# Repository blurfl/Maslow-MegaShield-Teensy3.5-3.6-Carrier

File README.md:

# Maslow-MegaShield-Teensy3.5-3.6-Carrier
Carrier board to connect a Teensy 3.5 or 3.6 to a Maslow MegaShield motor control board
======================

***
Layout

***
Schematic

***
Notes

 Most of the pin assignments match the Arduino Mega. IN5 & IN6 were changed so that they would be PWM capable (for a different project). The AUX pins were re-arranged for convenience of layout. The board version detection was not implemented, as that would tie up four more gpio pins. 
 
 There is provision to choose the voltage used for the encoders, either the 5V from the USB connection or the 3V3 regulated by the Teensy. It is strapped for 3V3, and that seems to work well on the Teensy 3.5 I've tested. The Teensy 3.6 would be damaged by using more than 3V3 in its inputs.

 The JTAG parts are not tested.

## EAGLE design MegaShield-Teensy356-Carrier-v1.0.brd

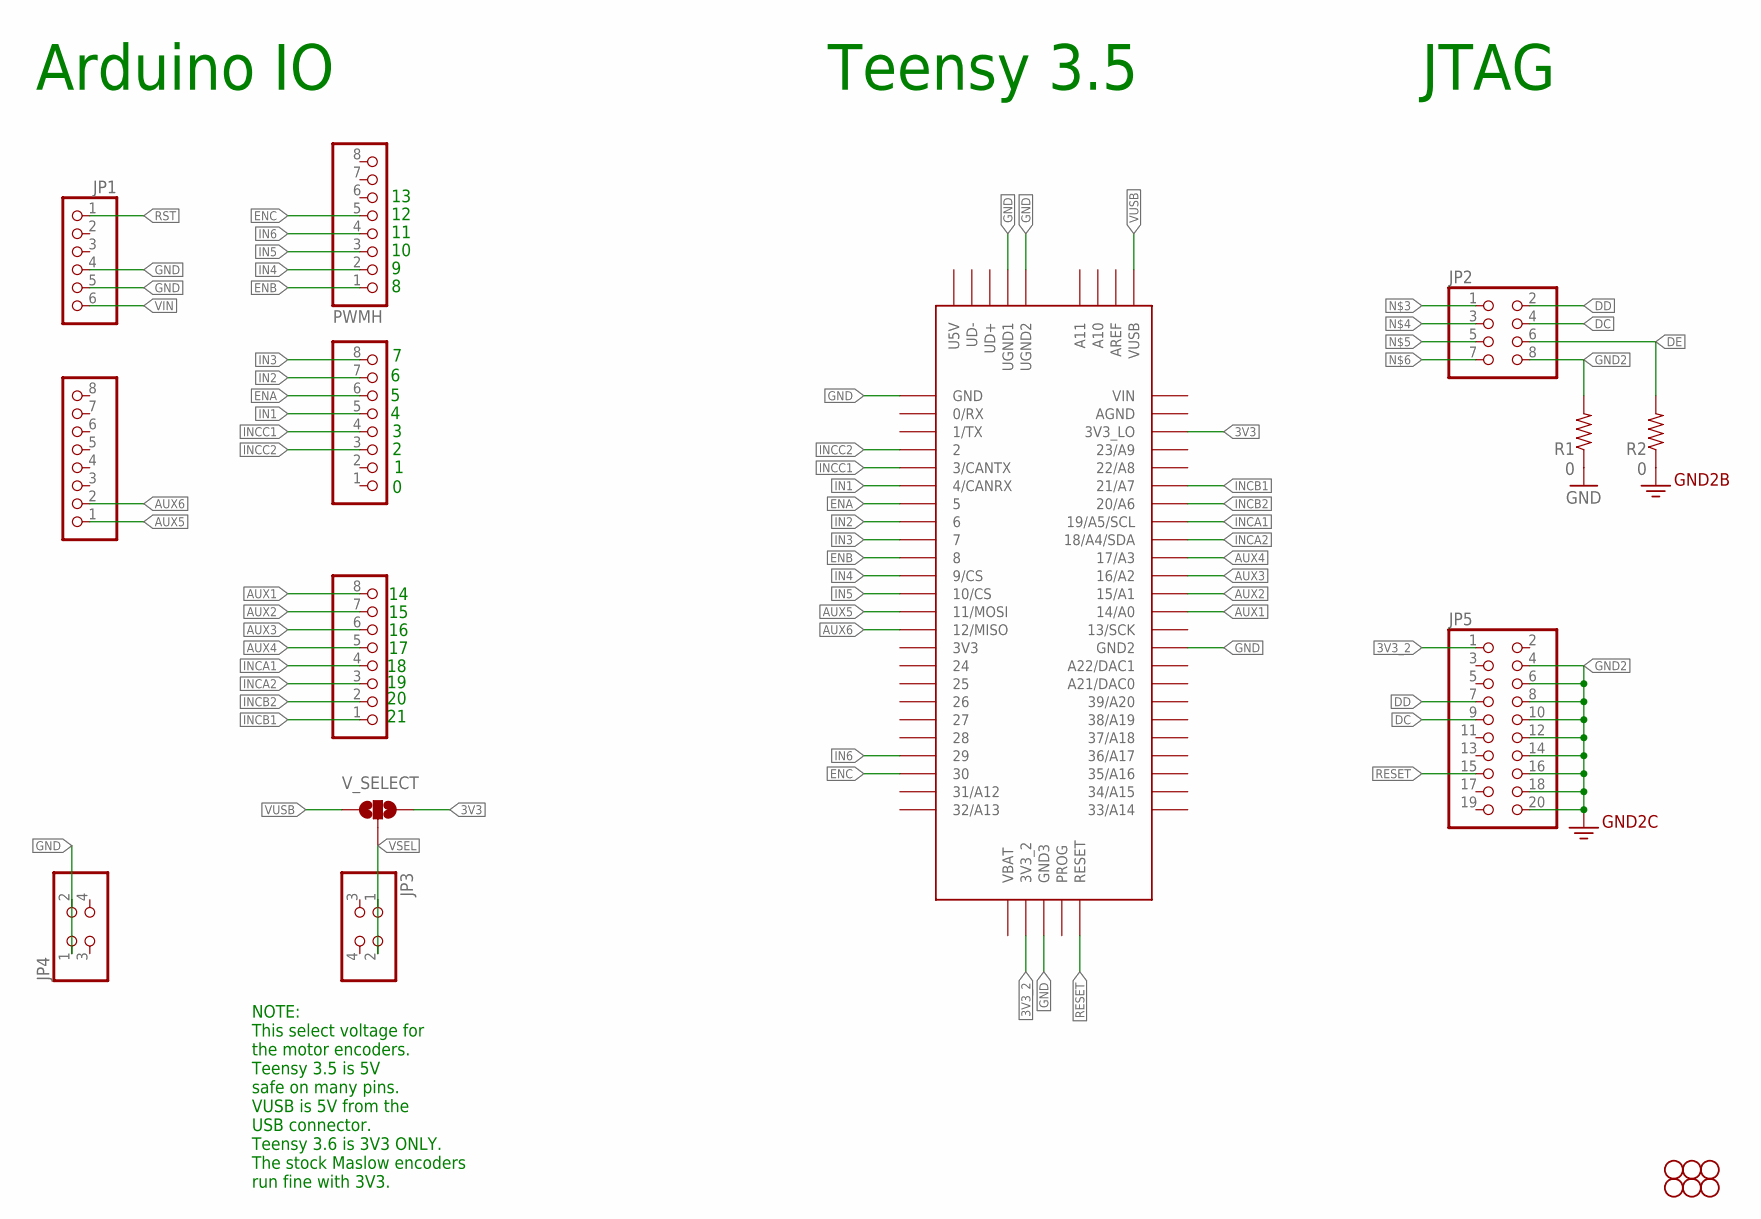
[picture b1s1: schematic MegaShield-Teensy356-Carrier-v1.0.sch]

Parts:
COMMUNICATION, COMMUNICATION1: PINHD-1X8; 1X08
H1, H2, H3, H4, H5, H6: STAND-OFF
JP1: PINHD-1X6; 1X06
JP2: PINHD-2X4; 2X04
JP3, JP4: PINHD-2X2; 2X02
JP5: PINHD-2X10; 2X10
PWMH: PINHD-1X8; 1X08
PWML: PINHD-1X8; 1X08
R1, R2: 0; 0603
U$15: TEENSY_3.5/3.6
V_SELECT: SOLDERJUMPER_2WAYT; SJ_2

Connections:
3V3: U$15.3V3_LO, V_SELECT.3
3V3_2: JP5.1, U$15.3V3_2
AUX1: COMMUNICATION.8, U$15.14/A0
AUX2: COMMUNICATION.7, U$15.15/A1
AUX3: COMMUNICATION.6, U$15.16/A2
AUX4: COMMUNICATION.5, U$15.17/A3
AUX5: COMMUNICATION1.1, U$15.11/MOSI
AUX6: COMMUNICATION1.2, U$15.12/MISO
DC: JP2.4, JP5.9
DD: JP2.2, JP5.7
DE: JP2.6, R2.2
ENA: PWML.6, U$15.5
ENB: PWMH.1, U$15.8
ENC: PWMH.5, U$15.30
GND: JP1.4, JP1.5, JP4.1, JP4.2, R1.1, U$15.GND, U$15.GND2, U$15.GND3, U$15.UGND1, U$15.UGND2
GND2: JP2.8, JP5.4, JP5.6, JP5.8, JP5.10, JP5.12, JP5.14, JP5.16, JP5.18, JP5.20, R1.2, R2.1
IN1: PWML.5, U$15.4/CANRX
IN2: PWML.7, U$15.6
IN3: PWML.8, U$15.7
IN4: PWMH.2, U$15.9/CS
IN5: PWMH.3, U$15.10/CS
IN6: PWMH.4, U$15.29
INCA1: COMMUNICATION.4, U$15.19/A5/SCL
INCA2: COMMUNICATION.3, U$15.18/A4/SDA
INCB1: COMMUNICATION.1, U$15.21/A7
INCB2: COMMUNICATION.2, U$15.20/A6
INCC1: PWML.4, U$15.3/CANTX
INCC2: PWML.3, U$15.2
RESET: JP5.15, U$15.RESET
RST: JP1.1
VIN: JP1.6
VSEL: JP3.1, JP3.2, V_SELECT.2
VUSB: U$15.VUSB, V_SELECT.1

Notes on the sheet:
Arduino IO
Teensy 3.5
NOTE: This select voltage for the motor encoders. Teensy 3.5 is 5V safe on many pins. VUSB is 5V from the USB connector. Teensy 3.6 is 3V3 ONLY. The stock Maslow encoders run fine with 3V3.
JTAG

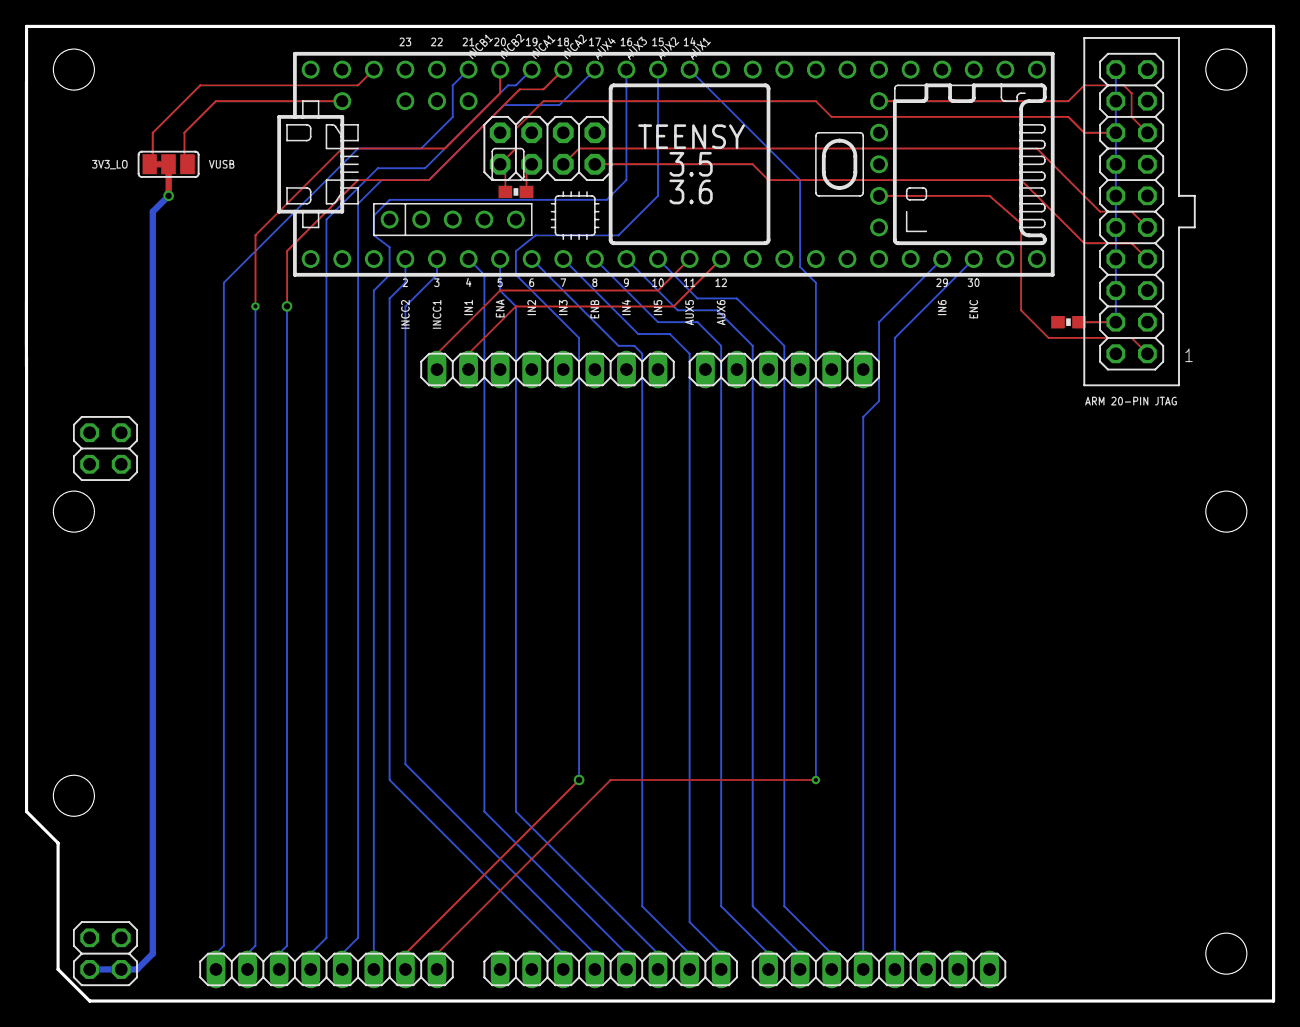
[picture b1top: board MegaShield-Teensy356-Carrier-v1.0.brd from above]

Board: 2 copper layers, 100.3 x 78.4 mm, 19 parts (0 on the bottom side), 31 nets.

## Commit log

2017-11-10 Initial file import
2017-11-10 edit README
2017-11-10 fix file name in README
2017-11-10 correct quantities
2017-11-10 tabs to spaces
2017-11-10 ignore Copper settings file
    Copper app keeps settings alongside board and schematic
2017-11-10 add to the parts not listed
2017-11-10 ignore EagldCad backup files
2017-11-10 update gitignore
2017-11-10 polish README
2017-11-10 further polishing of README
2017-11-10 more work on README

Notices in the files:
parts and their libraries:
SparkFun-Hardware: Licensing: Creative Commons ShareAlike 4.0 International - https://creativecommons.org/licenses/by-sa/4.0
SparkFun: Licensing: CC v3.0 Share-Alike You are welcome to use this library for commercial purposes.
